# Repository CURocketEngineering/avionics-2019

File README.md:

## Deprecated
For more information, visit the [new, Python implementation](https://github.com/CURocketEngineering/avionics_main).

### About
Clemson University Rocket Engineering (CURE) Avionics subteam program files. 
Powers CURE's competitive and non-competitive rockets. Used in the 
Intercollegiate Rocket Engineering Competition. Begun by Foster McLane, 2016.

### Documentation
* [`base/`](base/)
  * Code ran on the CURE base station for communication and telemetry
  * `main.py` for basic communication
  * `mpl.py` for graphical interpretation
  * `mpl_simulator.py` for simulating graphical interpretation
* [`cad/`](/cad)
  * Files for electrically engineering components in `eagle`
* [`data/`](data/)
  * Flight data
  * `jsongrapher.py` for ensuring simulation (and actual) data 
  * ['Complete simulation'](data/sim_data_graphed) for pictures of complete simulations
* [`extra/`](extra/)
  * Testing
  * GPS and XBEE `.ino` files
* [`main/`](main/)
  * Code ran on CURE rockets used for data collection, state changes, and telemetry
* [`pics/`](pics/)
  * Pictures used in this github
* [`xbee/bypass/`](xbee/bypass/)
  * Communication

### License
This project is licensed used the GNU General Public License v3.0

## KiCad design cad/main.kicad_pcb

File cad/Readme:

Sparkfun Names of sensors (in eagle "add" component):
   1. Venus GPS ->                   GPS/ VENUS638FLPX-L
   2. Atmospheric Sensor Breakout -> Sensors/ BME280
   3. 9DoF Sensor Stick ->           Sensors/ LSM9DS1
   4. Antenna ->                     RF/ XBEE

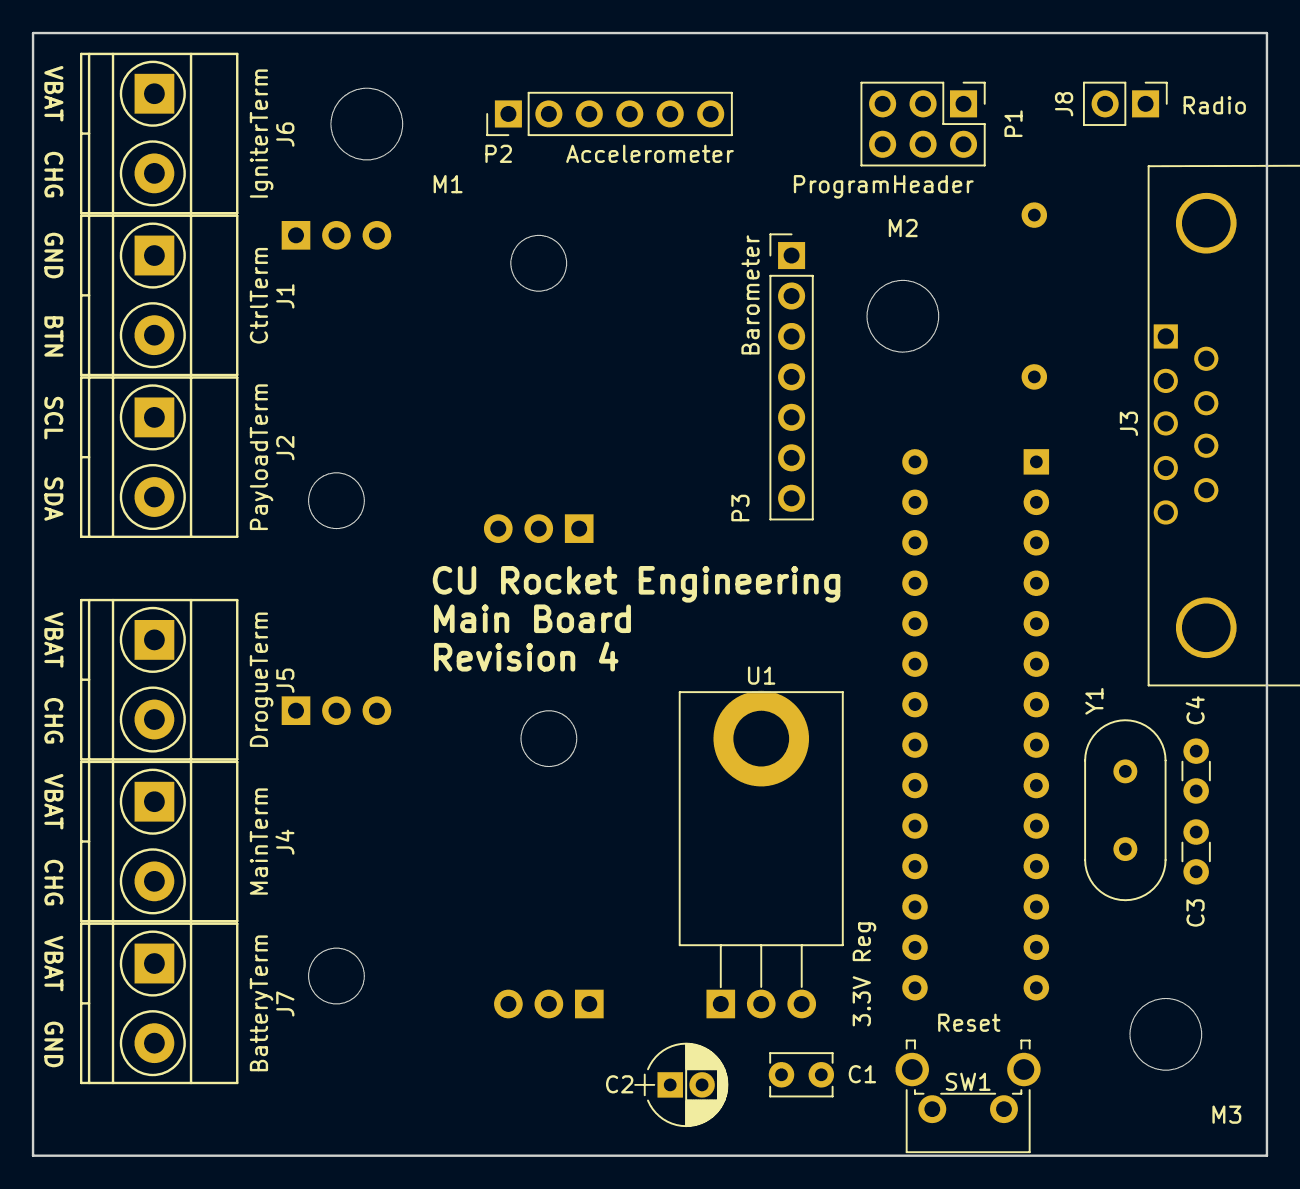
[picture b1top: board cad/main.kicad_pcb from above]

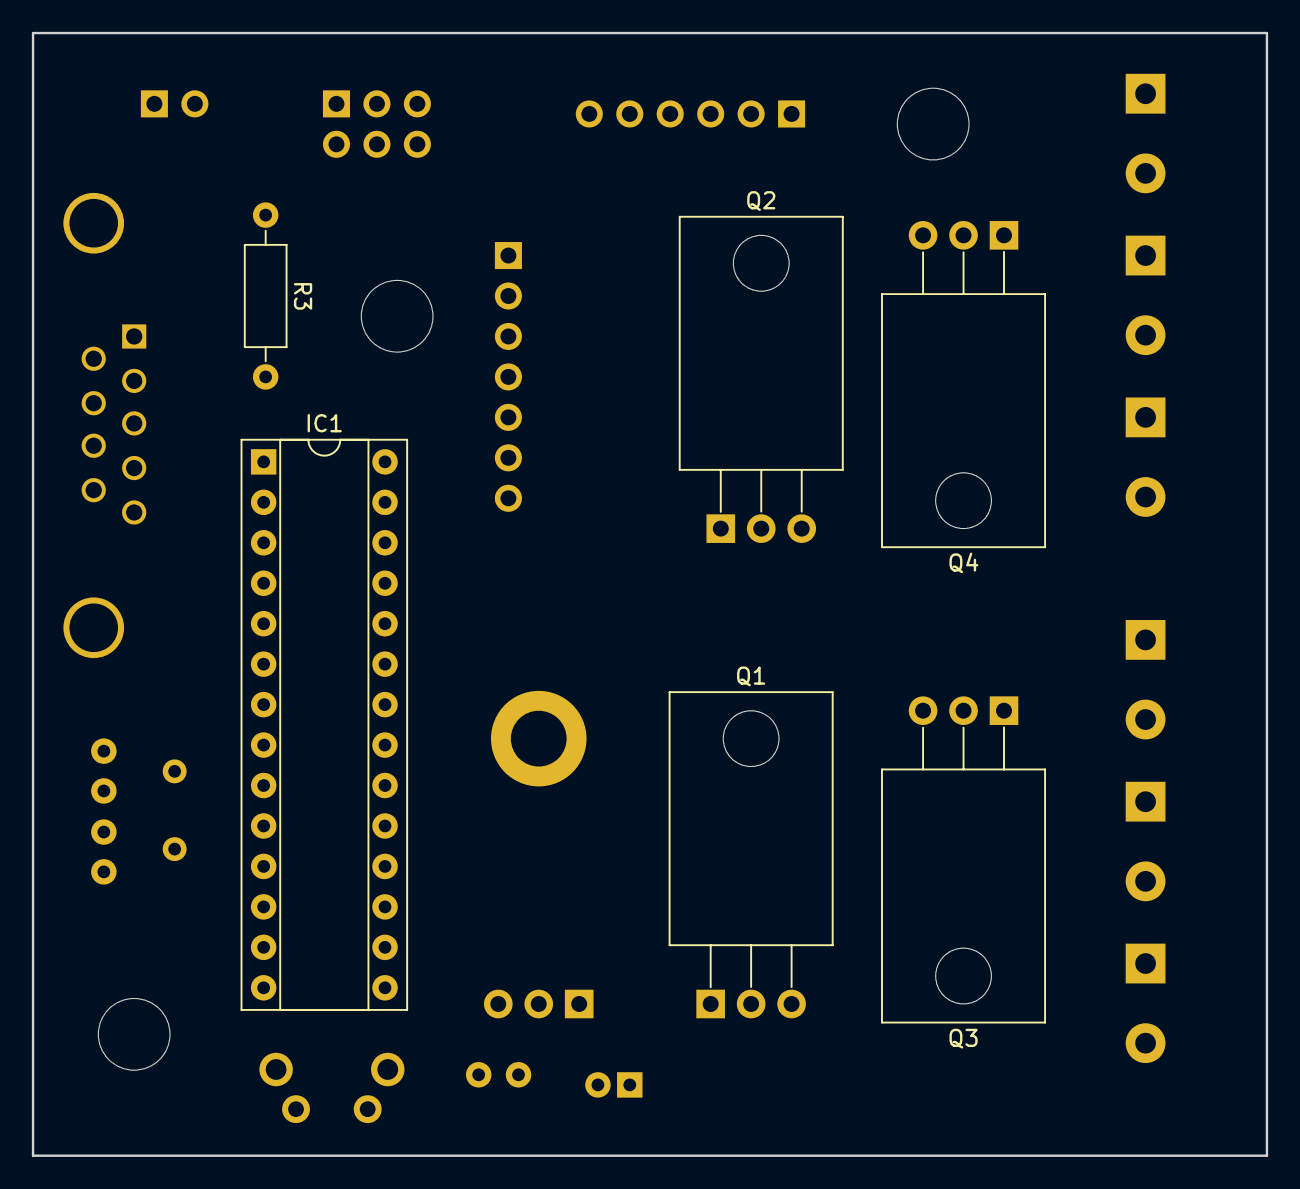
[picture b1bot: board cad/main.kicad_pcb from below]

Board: 2 copper layers, 77.5 x 70.5 mm, 27 parts (6 on the bottom side), 31 nets, no tracks yet.

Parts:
C1: 0.1 µF; C_Disc_D3.8mm_W2.6mm_P2.50mm
C2: 10 µF; CP_Radial_D5.0mm_P2.00mm
C3, C4: 27 pF; C_Disc_D3.0mm_W1.6mm_P2.50mm
IC1: AVR; DIP-28_W7.62mm_Socket
J1: CtrlTerm; TerminalBlock_Pheonix_MKDS1.5-2pol
J2: PayloadTerm; TerminalBlock_Pheonix_MKDS1.5-2pol
J3: PanelTerm; DB9FC
J4: MainTerm; TerminalBlock_Pheonix_MKDS1.5-2pol
J5: DrogueTerm; TerminalBlock_Pheonix_MKDS1.5-2pol
J6: IgniterTerm; TerminalBlock_Pheonix_MKDS1.5-2pol
J7: BatteryTerm; TerminalBlock_Pheonix_MKDS1.5-2pol
J8: Radio; Pin_Header_Straight_1x02_Pitch2.54mm
M1, M2, M3: Mount; MountingHole_4.5mm
P1: ProgramHeader; Pin_Header_Straight_2x03_Pitch2.54mm
P2: Accelerometer; Pin_Header_Straight_1x06_Pitch2.54mm
P3: Barometer; Pin_Header_Straight_1x07_Pitch2.54mm
Q1: MainCtrl; TO-220_Horizontal
Q2: ArmCtrl; TO-220_Horizontal
Q3: DrogueCtrl; TO-220_Horizontal
Q4: IgniterCtrl; TO-220_Horizontal
R3: 10 kΩ; R_Axial_DIN0207_L6.3mm_D2.5mm_P10.16mm_Horizontal
SW1: Reset; SW_Tactile_SPST_Angled_PTS645Vx39-2LFS
U1: 3.3V Reg; TO-220_Horizontal
Y1: 8 MHz Crystal; Crystal_HC49-U_Vertical

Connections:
GND: C1.2, C2.2, C3.1, C4.2, IC1.8, IC1.22, J1.1, J3.2, J7.2, P1.6, P2.2, P2.6, P3.2, P3.6, Q2.2, SW1.1, U1.1
unnamed: C3.2, IC1.10, Y1.2
unnamed: C4.1, IC1.9, Y1.1
unnamed: IC1.1, P1.5, R3.2, SW1.2
unnamed: IC1.2, J8.1
unnamed: IC1.3, J8.2
unnamed: IC1.4, J3.5
unnamed: IC1.5, J3.4
unnamed: IC1.6, J3.3
unnamed: IC1.11, Q1.1
unnamed: IC1.12, Q3.1
unnamed: IC1.13, J1.2
unnamed: IC1.14, P3.3
unnamed: IC1.15, P3.4
unnamed: IC1.16, P3.5
unnamed: IC1.17, P1.4
unnamed: IC1.18, P1.1
unnamed: IC1.19, P1.3
unnamed: IC1.23, P2.3
unnamed: IC1.24, P2.4
unnamed: IC1.25, P2.5
unnamed: IC1.26, Q4.1
unnamed: IC1.27, J2.2
unnamed: IC1.28, J2.1
unnamed: J3.6, Q2.1
unnamed: J4.2, Q1.3
unnamed: J5.2, Q3.3
unnamed: J6.2, Q4.3
unnamed: Q1.2, Q2.3, Q3.2, Q4.2
VBAT: C2.1, J4.1, J5.1, J6.1, J7.1, U1.3
VCC: C1.1, IC1.7, IC1.20, J3.1, P1.2, P2.1, P3.1, P3.7, R3.1, U1.2

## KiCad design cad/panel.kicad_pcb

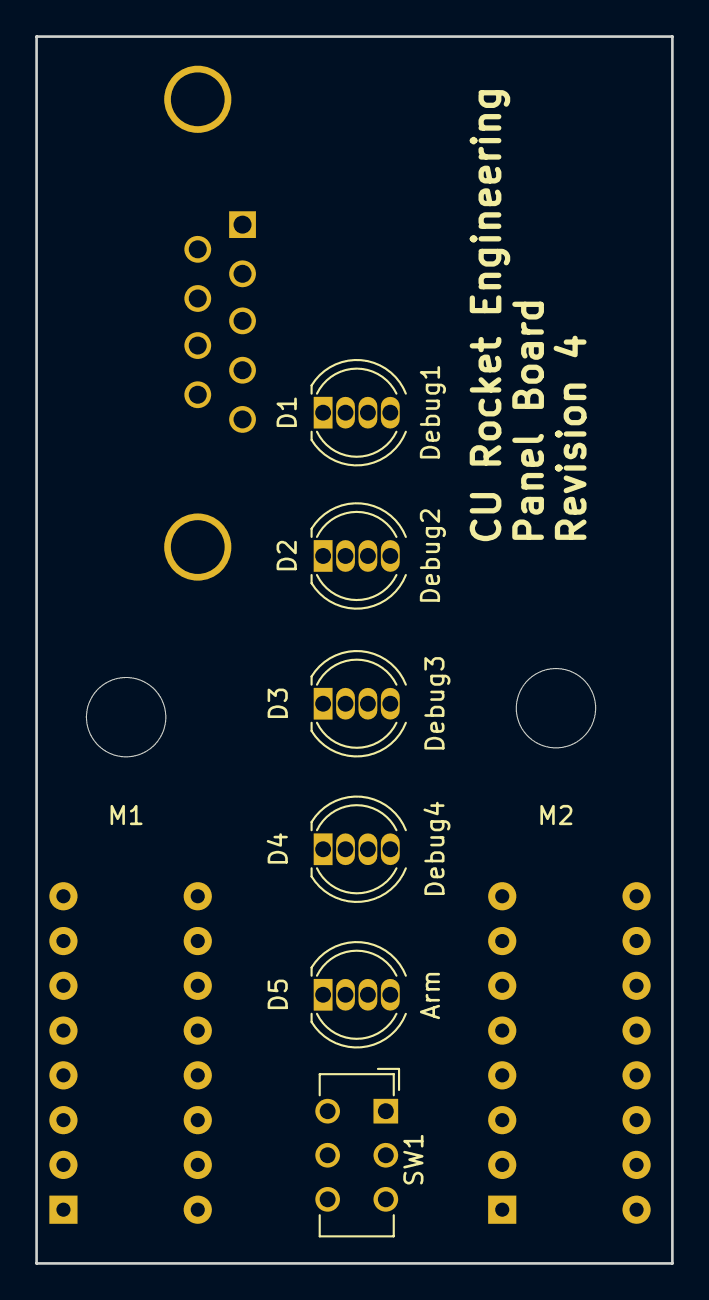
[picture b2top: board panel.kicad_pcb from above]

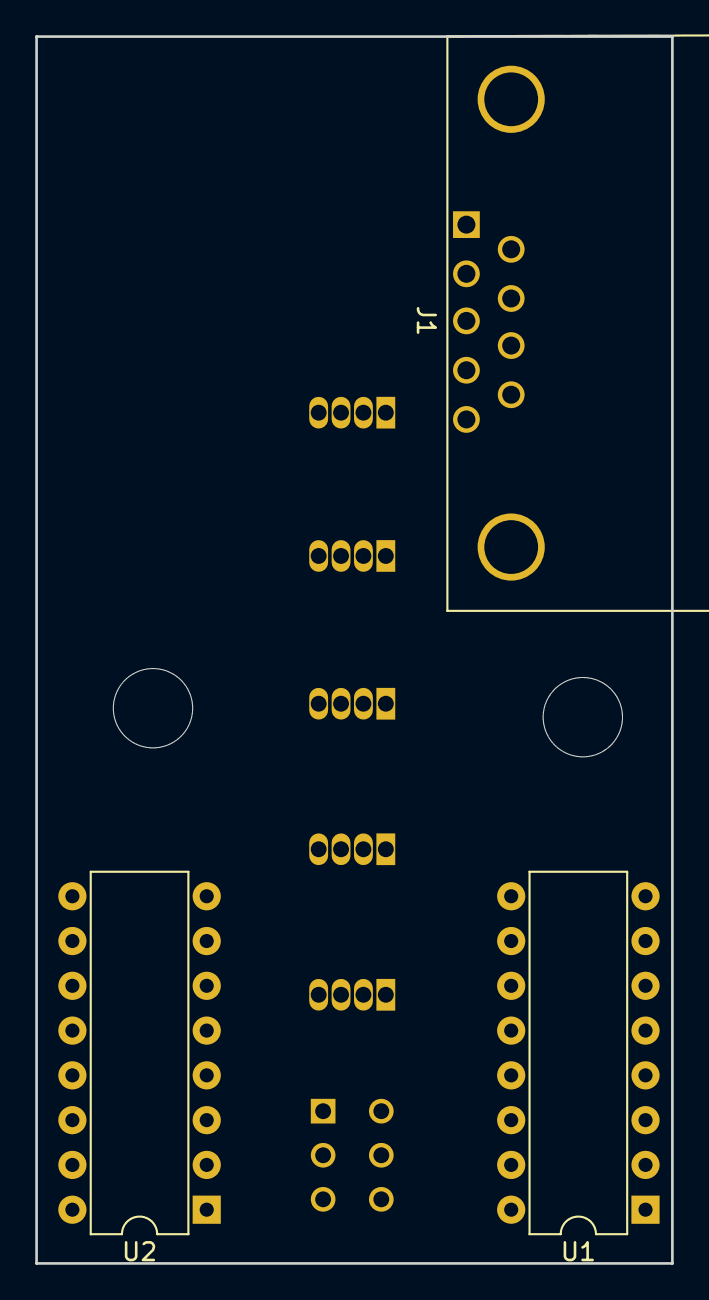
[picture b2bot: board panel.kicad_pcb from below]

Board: 2 copper layers, 36.1 x 69.6 mm, 11 parts (3 on the bottom side), 21 nets, no tracks yet.

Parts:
D1: Debug1; LED_D5.0mm-4
D2: Debug2; LED_D5.0mm-4
D3: Debug3; LED_D5.0mm-4
D4: Debug4; LED_D5.0mm-4
D5: Arm; LED_D5.0mm-4
J1: PanelTerm; DB9FC
M1, M2: Mount; MountingHole_4.5mm
SW1: Safety; SW_CuK_JS202011CQN_DPDT_Straight
U1, U2: 74HC595; DIP-16_W7.62mm

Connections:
GND: J1.2, SW1.1, SW1.4, U1.8, U1.13, U2.8, U2.13
unnamed: D1.1, U1.15
unnamed: D1.3, U1.2
unnamed: D1.4, U1.1
unnamed: D2.1, U1.3
unnamed: D2.3, U1.5
unnamed: D2.4, U1.4
unnamed: D3.1, U1.6
unnamed: D3.3, U2.15
unnamed: D3.4, U1.7
unnamed: D4.1, U2.1
unnamed: D4.3, U2.3
unnamed: D4.4, U2.2
unnamed: D5.3, U2.4
unnamed: D5.4, SW1.5
unnamed: J1.3, U1.14
unnamed: J1.4, U1.11, U2.11
unnamed: J1.5, U1.12, U2.12
unnamed: J1.6, SW1.2
unnamed: U1.9, U2.14
VCC: D1.2, D2.2, D3.2, D4.2, D5.2, J1.1, SW1.3, U1.10, U1.16, U2.10, U2.16

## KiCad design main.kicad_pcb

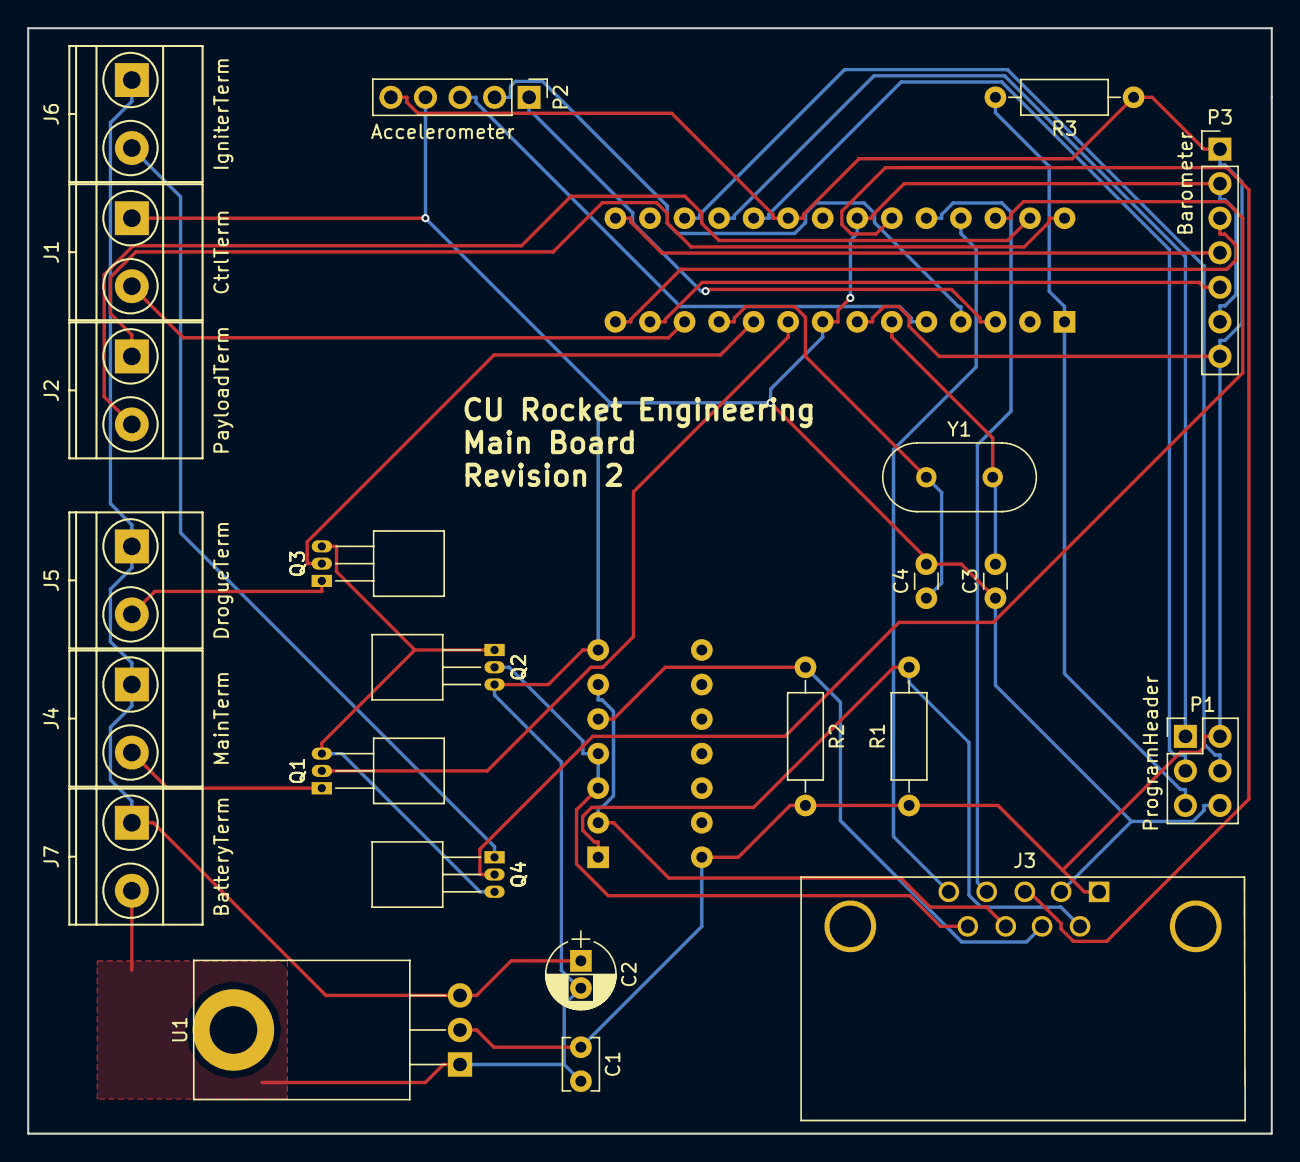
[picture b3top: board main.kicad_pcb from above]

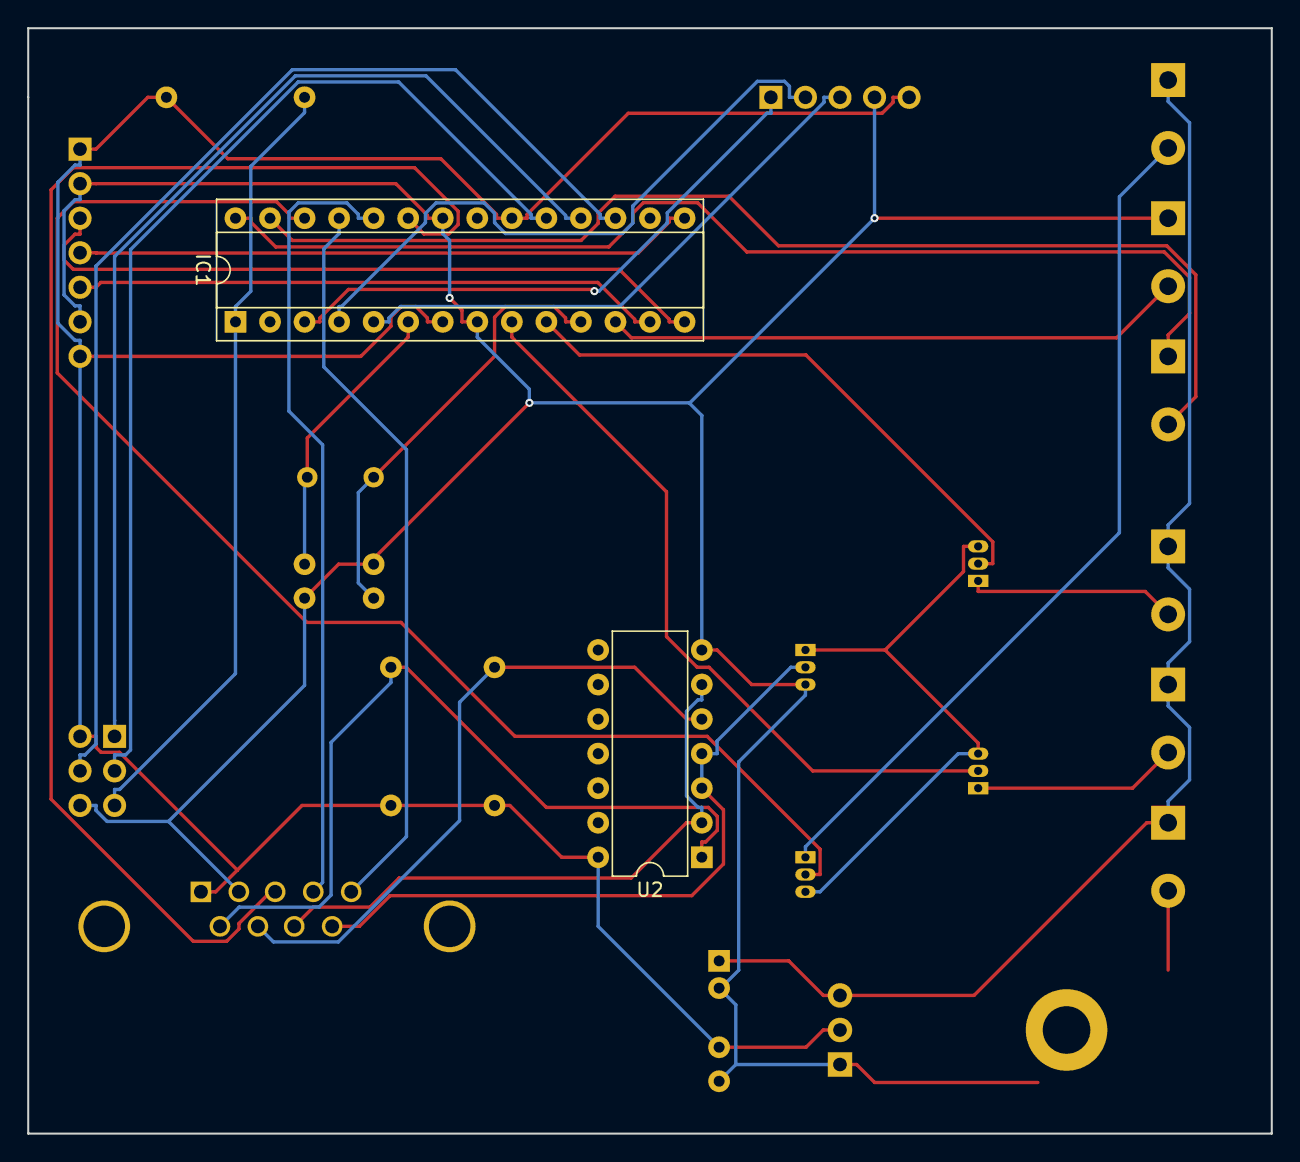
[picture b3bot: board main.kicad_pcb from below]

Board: 2 copper layers, 91.4 x 81.3 mm, 25 parts (2 on the bottom side), 32 nets.

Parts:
C1: 0.1 µF; C_Disc_D3.8mm_W2.6mm_P2.50mm
C2: 10 µF; CP_Radial_D5.0mm_P2.00mm
C3, C4: 22 pF; C_Disc_D3.0mm_W1.6mm_P2.50mm
IC1: AVR; DIP-28_W7.62mm_Socket
J1: CtrlTerm; TerminalBlock_Pheonix_MKDS1.5-2pol
J2: PayloadTerm; TerminalBlock_Pheonix_MKDS1.5-2pol
J3: PanelTerm; DB9FC
J4: MainTerm; TerminalBlock_Pheonix_MKDS1.5-2pol
J5: DrogueTerm; TerminalBlock_Pheonix_MKDS1.5-2pol
J6: IgniterTerm; TerminalBlock_Pheonix_MKDS1.5-2pol
J7: BatteryTerm; TerminalBlock_Pheonix_MKDS1.5-2pol
P1: ProgramHeader; Pin_Header_Straight_2x03_Pitch2.54mm
P2: Accelerometer; Pin_Header_Straight_1x05_Pitch2.54mm
P3: Barometer; Pin_Header_Straight_1x07_Pitch2.54mm
Q1: MainCtrl; TO-92_Horizontal1_Inline_Narrow_Oval
Q2: ArmCtrl; TO-92_Horizontal1_Inline_Narrow_Oval
Q3: DrogueCtrl; TO-92_Horizontal1_Inline_Narrow_Oval
Q4: IgniterCtrl; TO-92_Horizontal1_Inline_Narrow_Oval
R1, R2, R3: 10 kΩ; R_Axial_DIN0207_L6.3mm_D2.5mm_P10.16mm_Horizontal
U1: 3.3V Reg; TO-220_Horizontal
U2: 74LS00; DIP-14_W7.62mm
Y1: Crystal; Crystal_HC49-U_Vertical

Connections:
GND: C1.2, C2.2, C3.1, C4.2, IC1.8, IC1.22, J1.1, J3.2, J7.2, P1.6, P2.4, P3.2, P3.6, Q2.3, U1.1, U2.7
unnamed: C3.2, IC1.6, Y1.2
unnamed: C4.1, IC1.11, Y1.1
unnamed: IC1.1, P1.5, R3.2
unnamed: IC1.3, P2.1
unnamed: IC1.4, P2.2
unnamed: IC1.5, P2.3
unnamed: IC1.9, Q1.2
unnamed: IC1.10, Q3.2
unnamed: IC1.12, J1.2
unnamed: IC1.13, P3.5
unnamed: IC1.14, P3.3
unnamed: IC1.15, P3.4
unnamed: IC1.17, P1.4
unnamed: IC1.18, P1.1
unnamed: IC1.19, P1.3
unnamed: IC1.23, J3.3
unnamed: IC1.24, J3.4
unnamed: IC1.25, J3.5
unnamed: IC1.26, Q4.2
unnamed: IC1.27, J2.2
unnamed: IC1.28, J2.1
unnamed: J3.6, R1.2, U2.1
unnamed: J3.7, R2.1, U2.5
unnamed: J3.8, U2.2, U2.6
unnamed: J3.9, Q2.2, U2.3, U2.4
unnamed: J4.2, Q1.1
unnamed: J5.2, Q3.1
unnamed: J6.2, Q4.1
unnamed: Q1.3, Q2.1, Q3.3, Q4.3
VBAT: C2.1, J4.1, J5.1, J6.1, J7.1, U1.3
VCC: C1.1, IC1.7, IC1.20, J3.1, P1.2, P2.5, P3.1, P3.7, R1.1, R2.2, R3.1, U1.2, U2.14

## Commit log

2017-03-02 add basic kicad project
2017-03-02 add wip schematic
2017-03-06 add more wip main schematic
2017-03-08 add completed panel schematic revision 1
2017-03-08 add mostly complete main section
2017-03-08 finalize main section
2017-03-28 add preliminary boards
2017-04-18 update main board with more compact footprint
2017-04-18 adjust regulator pad
2017-04-25 add board outlines
2017-04-25 remove payload project
2017-05-09 patch in arming LED and fix backwards power caps
2017-05-09 fill zone for main board
2017-05-09 fix wiring of latch
2017-05-09 add pull-up resistor to reset pin
2017-05-09 move cad files to cad folder and add skeleton source code
2017-05-10 force initial button state and fix crystal pins
2017-05-10 reconnect accelerometer to adc pins
2017-05-10 add relevant data files directory
2017-05-10 swap ready and reset buttons
2017-05-11 add more misc board fixes
2017-05-15 add sample flight data file
2017-05-15 add XBee example programs
2017-05-16 moving main board information out of the way
2017-05-16 adjust which values are silkscreened
2017-05-16 add heading comments
2017-05-16 add mounting holes
2017-05-16 fix accelerometer connection
2017-05-16 add code to measure accelerometer and barometer data
2017-05-16 add mapping values
2017-05-19 add transmission attempts to latency
2017-05-19 add state machine to main program
2017-05-19 separate main and payload programs
2017-05-20 add flight logic
2017-05-28 fix syntax and turn off terminal connections on halt
2017-06-01 break up fall phase and make all LEDs being green meaning successful recovery
2017-06-09 add absolute altitude calculation
2017-06-09 increase precision of altitude calculation
2017-06-09 fix unconnected GND net in panel
2017-06-09 add pressure to flight data
2017-06-09 add debug mode which reads sensors from serial
2017-06-09 add test program which simulates sensor values and payload
2017-06-09 fill out pin numbers and allow programming with usbtiny
2017-06-10 change LEDs to command anode and release rev 3
2017-06-10 add support for continuing flight even if main computer resets
2017-06-10 add automatic board detection based on directory
2017-06-10 fix port numbers and save debug LEDs in EEPROM
2017-06-11 add diode after flop and start hand-made traces
2017-06-11 change board back to uno until we have 8MHz crystal/resonator
2017-06-11 fix LED output and store ground in EEPROM
2017-06-12 change payload addr to 8
2017-06-12 fix backwards MOSFETs
2017-06-16 adjust pinout to revision 2.718281828459045
2017-06-16 update programming for circuit board
2017-06-16 make main program give a little more startup information
2017-06-16 make test program use PROGMEM
2017-06-20 move to revision 4 of boards
2017-06-20 add LED test
2017-06-20 add more serial debug to test
2017-06-20 update altimeter setting for Truth or Consequences
2017-06-20 fix edge cuts on panel
2017-06-20 add startup delay for main computer when debugging
2017-06-20 rename debug to radio header
2017-06-21 attempt to use utf8 in serial monitor
2017-06-21 add basic payload program structure
2017-06-21 rename XBeeProgram to XBeePass
2017-06-21 rename payload time to timing to avoid name clash
2017-06-22 switch payload communication to UART instead of I²C
2017-06-22 update kicad project files
2017-06-22 add payload sensor data and communication
2017-06-22 remove remaining references to Wire
2017-06-22 make dp a signed integer
2017-06-22 rearrange payload<->computer interaction and update barometer reading code
2017-06-22 adjust test flight data for new units
2017-06-22 update payload comm for new units
2017-06-22 update altimeter reading
2017-06-22 setup finished communication between main<->payload<->base
2017-06-22 change to python2
2017-06-22 fix uarts and disable missing sensors
2017-06-22 add more python to gitignore
2017-06-22 disable sound as well
2017-06-22 remove unused init calls
2017-06-22 fix sound init
2017-06-22 fix init assignment in sound
2017-06-22 fix box arguments
2017-06-22 fix misnamed label
2017-06-22 fix another variable
2017-06-22 more fixes
2017-06-22 disable magnetometer too
2017-06-22 more unfound fixes
2017-06-22 disable more stuff
2017-06-22 fix state reference
2017-06-22 have more code
2017-06-22 more code...
2017-06-22 print data transfered
2017-06-22 add more python2 compatibility
2017-06-22 make gps fail on unexpected input
2017-06-22 add GPS size safeguard
2017-06-22 add working GPS
2017-06-22 fix radio uart
2017-06-22 do radio over USB OTG
2017-06-23 add payload arduino GPS code
2017-06-23 add working GPS program
2017-06-23 make payload get GPS over I²C
2017-06-23 use i2c correctly in gps
2017-06-23 fix error in test program
2017-06-23 add encoding to python program
2017-06-23 use floats for macro defines
2017-06-23 add state names and remote disarm
2017-06-23 adjust max ignite time
2017-06-24 add blackbox in base station as well
2017-06-24 make small misc payload fixes
2017-06-25 reenable payload stuff
2017-06-25 separate main and extra programs
2017-10-08 update base program for main computer with GPS
2017-10-08 move XBeePass to prog
2017-10-08 read GPS and contact base station
2017-10-09 fix blackbox import
2017-10-12 remove dependence of payload on main computer
2017-10-12 Remove wire protocol in GPS program
2017-10-13 make SoftwareSerial optional in XBeeEcho
2017-10-13 use tested readGps function
2017-10-13 fix whitespace
2017-10-13 change board definition for Main
2017-10-13 add working copies
2017-10-13 make idle rerun each tick
2017-10-13 rate limit idle
2017-10-13 make comm more resilient
2017-10-13 ignore blackbox files
2017-10-13 fix gps comm
2017-11-08 remove debug stuff
2017-11-08 fix small pointless kicad issue
2017-11-15 remove cad files
2017-11-15 remove atmega328w.png
2017-11-29 Split main_v0.2
    Split apart the initial main v0.2 file into main.ino and various .h/.cpp files. Compiles correctly on (Windows) Arduino IDE and PlatformIO (Atom package).
2017-12-03 add wip refactoring for function names
2018-01-11 move global to pins and separate debug
2018-01-16 add json.h
2018-01-23 Initial 9DoF sensor calculations
    This is not integrated at all with the rest of the /main files. This is a preliminary idea as to how the 9DoF sensor may be implemented in the future. Deviation calculations use the gyroscope's X and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
    Uses Arduino's Serial.print to display data in the Serial Monitor (usually located in the Arduino IDE; not sure if Linux is able to view this).
    The programs should theoretically work, but no testing has been done.
    Requires the SparkFunLSM9DS1.h library (located https://github.com/sparkfun/SparkFun_LSM9DS1_Arduino_Library).
2018-01-29 An attempt to incorporate the new barometer.
2018-01-31 Added in JSON
    Hopefully everything works, this is the first time I worked with JSON in any form.
2018-02-07 Fixed some barometer things
2018-02-07 9DoF and other edits
2018-02-15 update automatically finding the Arduino dir in macOS
2018-02-15 move libraries
2018-02-15 Create Schematics and Data Sheets
2018-02-20 add sparkfun lsm9ds1 library
2018-02-20 move libraries to main folder
2018-02-21 bring barometer up to speed
2018-02-21 move functions out of gps
2018-02-22 update communication for json
2018-02-22 dos2unix all of the files and add datalogging
2018-03-06 add GPS date/time and add compilation fixes
2018-03-06 rename Datasheets and Schematics to cad
2018-03-06 finish new communication
2018-03-06 clean up cad a little
2018-03-08 2018-03-07 changes
2018-03-08 Removed struct, added json.
2018-03-08 quickfix
2018-03-14 clean up style (i.e. remote end-of-line whitespace)
2018-03-14 change to new comm standard
2018-03-14 fix little issues in communication.cpp
2018-03-15 update cad for combined i2c
2018-03-15 make gps use serial2
2018-03-15 remove compiler warnings
2018-03-15 ignore backup cad files
2018-03-16 add LSM/BME test code
2018-03-16 fix python syntax error
2018-03-18 print a newline to serial after message
2018-03-24 fix barometer reading
2018-03-24 add attitude to sensor output
2018-03-24 fix issue with same data across 9dof sensor
2018-03-24 move pins to pins.h
2018-03-28 urwid base
2018-03-28 Initial creation of init and update functions
2018-03-28 Fixed some issues as per Harrison
2018-03-28 fixes
2018-03-28 trying threading lol
2018-03-28 added fake data and created accompanying function
2018-03-28 add control switch
2018-03-29 adjust base station for new json
2018-04-04 urwid update
2018-04-04 Updated urw.py
2018-04-04 add emulator for csv data
2018-04-04 Updates single graph completely
2018-04-04 quickupdate
2018-04-04 commented
2018-04-04 replace fix
2018-04-05 continually send none command
2018-04-05 make halt go to idle instead of sleeping the processor
2018-04-06 plotting code
2018-04-06 add parse to mpl.py
2018-04-06 hotfix
2018-04-09 Some experimentation with mpl
2018-04-11 Test fixes.
2018-04-11 Removed comm.init(), must wait to show fake data if error.
2018-04-12 add simulation
2018-04-18 add sim data
2018-04-18 ifdef flight.h
2018-04-19 color fix for comm graphs
2018-05-21 remove unused payload code
2018-05-21 Added Board and Schematic files
2018-05-30 Added speed function and makeshift speedometer
2018-06-05 miscellaneous changes
2018-06-06 allow XBeePass to use SoftwareSerial
2018-06-13 Begun work on simulation for fake data
2018-06-13 add SS for XBeeLatency
2018-06-13 move cad files
2018-06-14 fix main program
2018-06-18 graphed sim data
2018-06-18 adjust XBee communication
2018-06-18 remove pin collision
2018-06-18 move XBeePass
2018-06-19 fix datalog
2018-06-19 add XBeeBypass
2018-06-19 add possible delay before ejecting parachute
2018-06-20 make a few IREC changes
2018-06-21 more irec changes
2018-06-23 create teensy makefile
2018-06-23 move stuff to config.h
2018-06-23 add bypass src.uart
2018-06-23 remove bypass src.uart
2018-06-23 add speeds selector to makefile
2018-06-28 Updated graphing program
2018-07-07 make extra/makefile a link to main/makefile
2018-07-07 remove unnecessary sections from makefile
2018-07-07 make more irec changes
2018-07-07 automatically reboot on upload
2018-07-07 update makefile
2018-07-08 fix running make boards or make clean without setting speed
2018-09-21 license code under GPLv3
    enacted by all developers of the current program 2018-09-21
2018-09-24 adding readmes
2018-10-07 those qs
2018-10-07 read
2018-10-07 foster questions
2018-10-07 foster qs
2018-10-07 updated readme and moved eagle files
2018-10-07 moved files
2018-10-09 updated READMEs
2018-10-10 documentation and begin fixing mpl.py
2018-10-29 Visual with quickbox
2018-10-29 Updating for visual
2018-10-30 bug fix and visual example
2018-10-31 beta gui
2018-10-31 mpl documentation
2018-10-31 pre-meeting
2018-10-31 update ignore
2019-01-17 mpl.py major graphing update
2019-01-18 data area
2019-01-21 edited error msg
2019-04-24 bug fix update readmes
2019-05-17 Removed unecessary graphing
2019-05-28 updated for a new year
2019-05-29 fixed wire.h issue, and toggleRelay bug
2019-06-14 qwiic
2019-06-14 ejection test
2019-06-14 ready for ejection
2019-11-20 Made a note about deprecation in readme.
